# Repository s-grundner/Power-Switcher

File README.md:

# USB C Power Switcher

Device to digitally request power from USB C PD capable supplies

## Repository Structure

- [Documentation](/documentation/)
- [Manufacturing](/manufacturing/)
- [Simulations](/simulations/)
- [Source Code](/source/)

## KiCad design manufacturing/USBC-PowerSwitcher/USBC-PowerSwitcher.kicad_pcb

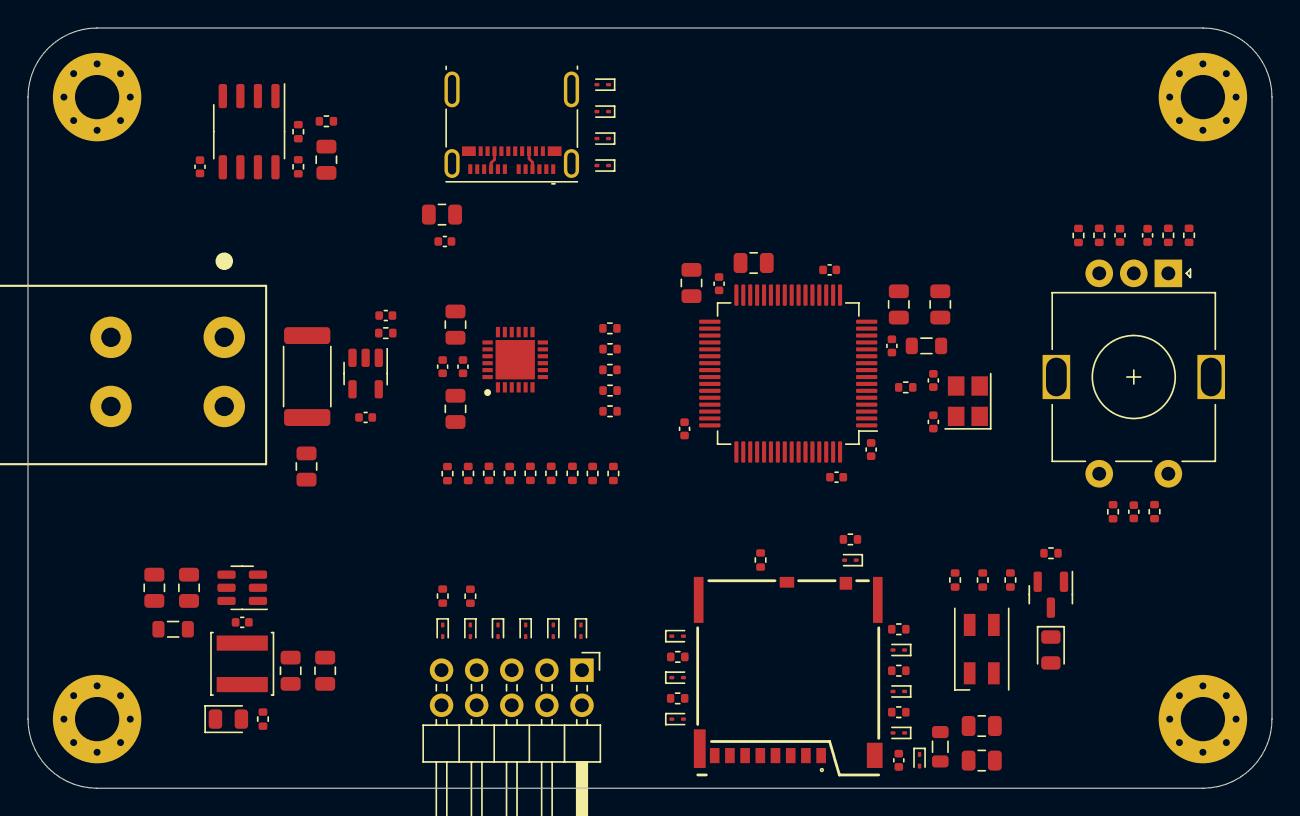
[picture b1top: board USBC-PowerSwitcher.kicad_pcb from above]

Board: 4 copper layers, 90.0 x 55.0 mm, 111 parts (0 on the bottom side), 64 nets.

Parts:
C1, C2, C8, C12, C13, C15, C17, C20, C21, C25, C26, C27, C28, C32, C33: 4u7; C_0805_2012Metric
C3, C4, C5, C6, C7, C11, C14, C16, C18, C19, C22, C23, C24, C29, C30, C31, C34: 100n; C_0402_1005Metric
C9, C10: 10p; C_0402_1005Metric
D1, D2, D3, D4, D5, D6, D9, D10, D11, D12, D13, D14, D15, D16, D17, D18, D19, D20: ESD9B3.3ST5G; D_SOD-923
D7, D21: RED; LED_0805_2012Metric
D8: LED_RGBA; LED_SK6812MINI_PLCC4_3.5x3.5mm_P1.75mm
FB1, FB2, FB3: 100R @ 100MHz; L_0805_2012Metric
J1: USB_C_Receptacle; USB_C_Receptacle_Molex_105450-0101
J2: SWD; PinHeader_2x05_P2.54mm_Horizontal
J3: VDC; TerminalBlock_WAGO_2604-1102
J5: Micro_SD_Card_Det1; 503398-1892
L1: 3u3; L_Sunlord_SWPA4030S
Q1: 2N7002; SOT-23
Q2: DMP3098LSD; SO-8_3.9x4.9mm_P1.27mm
R1, R39: 22R; R_0402_1005Metric
R2, R3, R8, R11, R17, R30, R31, R34, R35, R36, R37, R38: 20k; R_0402_1005Metric
R4, R5, R6, R7, R10, R12, R13, R14, R15, R16, R18, R19, R20, R21, R32, R40: 2k2; R_0402_1005Metric
R9: 12m; R_2512_6332Metric
R22, R23, R24, R25, R26, R27, R28, R29: R; R_0402_1005Metric
R33: 1M; R_0402_1005Metric
SW1: EC11N152440x; RotaryEncoder_Alps_EC11E-Switch_Vertical_H20mm
U1: STM32F412RGT6; LQFP-64_10x10mm_P0.5mm
U2: CYPD3177-24LQXQ; QFN50P400X400X60-25N-D
U3: INA180A2; SOT-23-5
U4: LMR50410-Q1; SOT-23-6
Y1: 16MHz 9pF; Crystal_SMD_3225-4Pin_3.2x2.5mm

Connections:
+3V3: C1.1, C4.1, C5.1, C6.1, C7.1, C8.1, C11.1, C14.1, C17.1, C18.1, C19.1, C27.1, C28.1, C32.1, D5.2 (A2), D8.4 (A), FB1.2, FB3.1, J2.1, L1.2, R4.1, R5.1, R6.1, R7.1, R10.1, R17.2, R22.1, R24.1, R26.1, R28.1, R30.2, R31.2, R34.2, R35.2, R36.2, R37.2, R38.2, R40.1, U1.1 (VBAT), U1.19 (VDD), U1.32 (VDD), U1.48 (VDD), U1.64 (VDD), U2.23 (VDDD), U3.5 (V+), U4.3 (FB)
+3V3A: C2.1, C3.1, FB1.1, U1.13 (VDDA)
/Digital/NPWM_B: R21.1, U1.62 (PB9)
/Digital/NPWM_G: R20.1, U1.61 (PB8)
/Digital/NPWM_R: R19.1, U1.59 (PB7)
/Digital/PD_FAULT: Q1.1 (G), R8.1, U1.39 (PC8), U2.9 (FAULT)
/Digital/PD_FLIP: R4.2, U1.37 (PC6), U2.10 (FLIP)
/Digital/PD_INT: R7.2, U1.42 (PA9), U2.7 (HPI_INT)
/Digital/PD_SAFE: R18.2, U1.36 (PB15)
/Digital/PD_SCL: R6.2, U1.41 (PA8), U2.13 (HPI_SCL)
/Digital/PD_SDA: R5.2, U1.56 (PB4), U2.12 (HPI_SDA)
/Digital/SWCLK: D3.2 (A2), J2.4, U1.49 (PA14)
/Digital/SWDIO: D4.2 (A2), J2.2, U1.46 (PA13)
/Digital/SWO: D2.2 (A2), J2.6, U1.55 (PB3)
/Digital/Strapping/BOOT0: D6.2 (A2), J2.8, R3.1, U1.60 (BOOT0)
/Digital/Strapping/HSE_IN: C10.1, U1.5 (PH0), Y1.1
/Digital/Strapping/HSE_OUT: R1.2, U1.6 (PH1)
/Digital/Strapping/NRST: D1.2 (A2), J2.10, R2.1, U1.7 (NRST)
/Digital/Strapping/XTAL_IN: C9.1, R1.1, Y1.3
/Digital/USB_D+: D10.2 (A2), J1.A6 (D+), J1.B6 (D+), U1.45 (PA12)
/Digital/USB_D-: D9.2 (A2), J1.A7 (D-), J1.B7 (D-), U1.44 (PA11)
/PD/CC1: D12.2 (A2), J1.A5 (CC1), U2.15 (CC1)
/PD/CC2: D11.2 (A2), J1.B5 (CC2), U2.14 (CC2)
/PD/FET_SW: R13.2, U2.3 (VBUS_FET_EN)
/PD/I-Mess/I_MEAS: C23.2, R14.1, U2.8 (GPIO_1)
/PD/PDP-Config/ISNK_COARSE: R26.2, R27.1, U2.5 (ISNK_COARSE)
/PD/PDP-Config/ISNK_FINE: R28.2, R29.1, U2.6 (ISNK_FINE)
/PD/PDP-Config/VBUS_MAX: R22.2, R23.1, U2.2 (VBUS_MAX)
/PD/PDP-Config/VBUS_MIN: R24.2, R25.1, U2.1 (VBUS_MIN)
/PD/VCCD: C20.1, U2.24 (VCCD)
/PD/VDC_OUT: C22.1, Q2.5 (D), Q2.6 (D), R9.1, U2.11 (VDC_OUT), U3.3 (+)
/SMPS/BUCK_CB: C24.1, U4.1 (CB)
/SMPS/BUCK_SW: C24.2, L1.1, U4.6 (SW)
/SMPS/BUCK_VIN: C26.1, FB2.2, U4.4 (EN), U4.5 (VIN)
/SMPS/LED_A: D21.2 (A), R40.2
/UI/ROT_A: C30.1, R15.1, R30.1
/UI/ROT_B: C29.1, R16.1, R31.1
/UI/ROT_SW: C31.1, R17.1, R32.2
/UI/SDIO_CLK: D14.2 (A2), R39.1
/UI/SDIO_CMD: D13.2 (A2), J5.3 (CMD), R36.1
/UI/SDIO_D0: D15.2 (A2), J5.7 (DAT0), R35.1
/UI/SDIO_D1: D16.2 (A2), J5.8 (DAT1), R34.1
/UI/SDIO_D2: D19.2 (A2), J5.1 (DAT2), R38.1
/UI/SDIO_D3: D18.2 (A2), J5.2 (DAT3/CD), R37.1
/UI/SD_CLK: J5.5 (CLK), R39.2
/UI/SD_DET: D17.2 (A2), J5.9 (DET), R33.1
/UI/VSD: C33.1, C34.1, D20.2 (A2), FB3.2, J5.4 (VDD)
GND: C1.2, C2.2, C3.2, C4.2, C5.2, C6.2, C7.2, C8.2, C9.2, C10.2, C11.2, C12.2, C13.2, C14.2, C15.2, C16.2, C17.2, C18.2, C19.2, C20.2, C23.1, C25.2, C26.2, C27.2, C28.2, C29.2, C30.2, C31.2, C32.2, C33.2, C34.2, D1.1 (A1), D2.1 (A1), D3.1 (A1), D4.1 (A1), D5.1 (A1), D6.1 (A1), D9.1 (A1), D10.1 (A1), D11.1 (A1), D12.1 (A1), D13.1 (A1), D14.1 (A1), D15.1 (A1), D16.1 (A1), D17.1 (A1), D18.1 (A1), D19.1 (A1), D20.1 (A1), D21.1 (K), J1.A1 (GND), J1.A12 (GND), J1.B1 (GND), J1.B12 (GND), J2.3, J2.5, J2.9, J3.3, J3.4, J5.6 (VSS), Q1.2 (S), R2.2, R3.2, R8.2, R23.2, R25.2, R27.2, R29.2, R33.2, SW1.C, SW1.S2, U1.12 (VSSA), U1.18 (VSS), U1.31 (VSS), U1.47 (VSS), U1.63 (VSS), U2.19 (GND), U2.22 (VSS), U2.25 (EPAD), U3.2 (GND), U4.2 (GND), Y1.2, Y1.4
unnamed: C21.2, C22.2, R11.2, R12.2, R13.1
unnamed: D7.2 (A), R10.2
unnamed: D7.1 (K), Q1.3 (D)
unnamed: D8.3 (BK), R21.2
unnamed: D8.2 (GK), R20.2
unnamed: D8.1 (RK), R19.2
unnamed: Q2.2 (G), Q2.4 (G), R12.1
unnamed: Q2.1 (S), Q2.3 (S)
unnamed: R14.2, U3.1
unnamed: R15.2, SW1.A
unnamed: R16.2, SW1.B
unnamed: R32.1, SW1.S1
unnamed: C15.1, U1.30 (VCAP_1)
unnamed: R18.1, U2.4 (SAFE_PWR_EN)
VBUS: C12.1, C16.1, C21.1, C25.1, FB2.1, J1.A4 (VBUS), J1.A9 (VBUS), J1.B4 (VBUS), J1.B9 (VBUS), Q2.7 (D), Q2.8 (D), R11.1, U2.18 (VBUS_IN)
VDC: C13.1, J3.1, J3.2, R9.2, U3.4 (-)

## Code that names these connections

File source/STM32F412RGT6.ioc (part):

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Mcu.Name=STM32F412R(E-G)Tx
Mcu.Package=LQFP64
Mcu.UserName=STM32F412RGTx
PA0.Signal=ADCx_IN0
PA1.Signal=ADCx_IN1
PA11.Mode=Device_Only
PA11.Signal=USB_OTG_FS_DM
PA12.Mode=Device_Only
PA12.Signal=USB_OTG_FS_DP
PA13.Mode=Trace_Asynchronous_SW
PA13.Signal=SYS_JTMS-SWDIO
PA14.Mode=Trace_Asynchronous_SW
PA14.Signal=SYS_JTCK-SWCLK
PA5.Mode=Full_Duplex_Master
PA5.Signal=SPI1_SCK
PA6.Mode=Full_Duplex_Master
PA6.Signal=SPI1_MISO
PA7.Mode=Full_Duplex_Master
PA7.Signal=SPI1_MOSI
PA8.Mode=I2C
PA8.Signal=I2C3_SCL
PA9.GPIOParameters=GPIO_Label
PA9.GPIO_Label=PD_INT
PA9.Signal=GPXTI9
PB15.GPIOParameters=GPIO_Label
PB15.GPIO_Label=PD_SAFE
PB15.Signal=GPIO_Input
PB3.Mode=Trace_Asynchronous_SW
PB3.Signal=SYS_JTDO-SWO
PB4.Mode=I2C
PB4.Signal=I2C3_SDA
PB6.Mode=SD_4_bits_Wide_bus
PB6.Signal=SDIO_D0
PB7.Signal=S_TIM4_CH2
PB8.Signal=S_TIM4_CH3
PB9.Signal=S_TIM4_CH4
PC1.GPIOParameters=GPIO_Label
PC1.GPIO_Label=ROT_A
PC1.Signal=GPXTI1
PC10.Mode=SD_4_bits_Wide_bus
PC10.Signal=SDIO_D2
PC11.Mode=SD_4_bits_Wide_bus
PC11.Signal=SDIO_D3
PC12.Mode=SD_4_bits_Wide_bus
PC12.Signal=SDIO_CK
PC2.GPIOParameters=GPIO_Label
PC2.GPIO_Label=ROT_B
PC2.Signal=GPXTI2
PC3.GPIOParameters=GPIO_Label
PC3.GPIO_Label=ROT_SW
PC3.Signal=GPXTI3
PC6.GPIOParameters=GPIO_Label
PC6.GPIO_Label=PD_Flip
PC6.Signal=GPIO_Input
PC7.GPIOParameters=GPIO_Label
PC7.GPIO_Label=PD_GPIO
PC7.Signal=GPXTI7
PC8.GPIOParameters=GPIO_Label
PC8.GPIO_Label=PD_Fault
PC8.Signal=GPIO_Input
PC9.Mode=SD_4_bits_Wide_bus
PC9.Signal=SDIO_D1
PD2.Mode=SD_4_bits_Wide_bus
PD2.Signal=SDIO_CMD
PH0\ -\ OSC_IN.Mode=HSE-External-Oscillator
PH0\ -\ OSC_IN.Signal=RCC_OSC_IN
PH1\ -\ OSC_OUT.Mode=HSE-External-Oscillator
PH1\ -\ OSC_OUT.Signal=RCC_OSC_OUT
RCC.HSE_VALUE=16000000
RCC.SYSCLKFreq_VALUE=96000000
RCC.SYSCLKSource=RCC_SYSCLKSOURCE_PLLCLK
board=custom

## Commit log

2023-08-25 upd BSB
2023-08-26 added Schematic
2023-08-26 upd README
2023-08-27 First Rough placement
